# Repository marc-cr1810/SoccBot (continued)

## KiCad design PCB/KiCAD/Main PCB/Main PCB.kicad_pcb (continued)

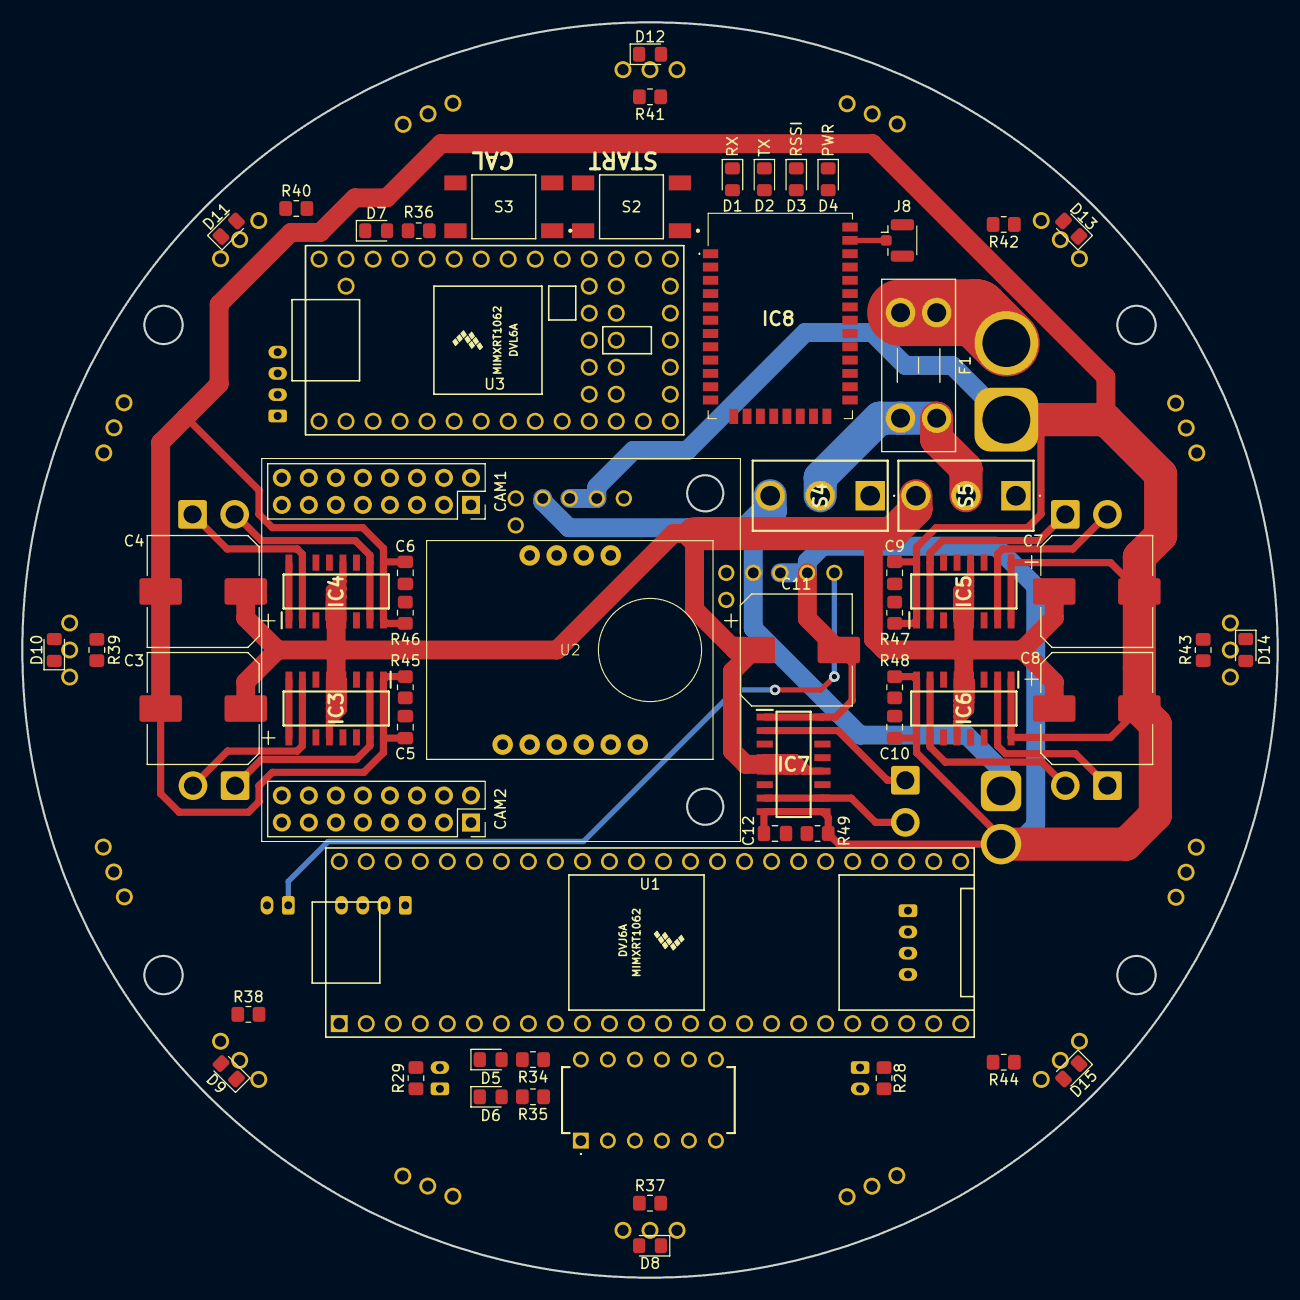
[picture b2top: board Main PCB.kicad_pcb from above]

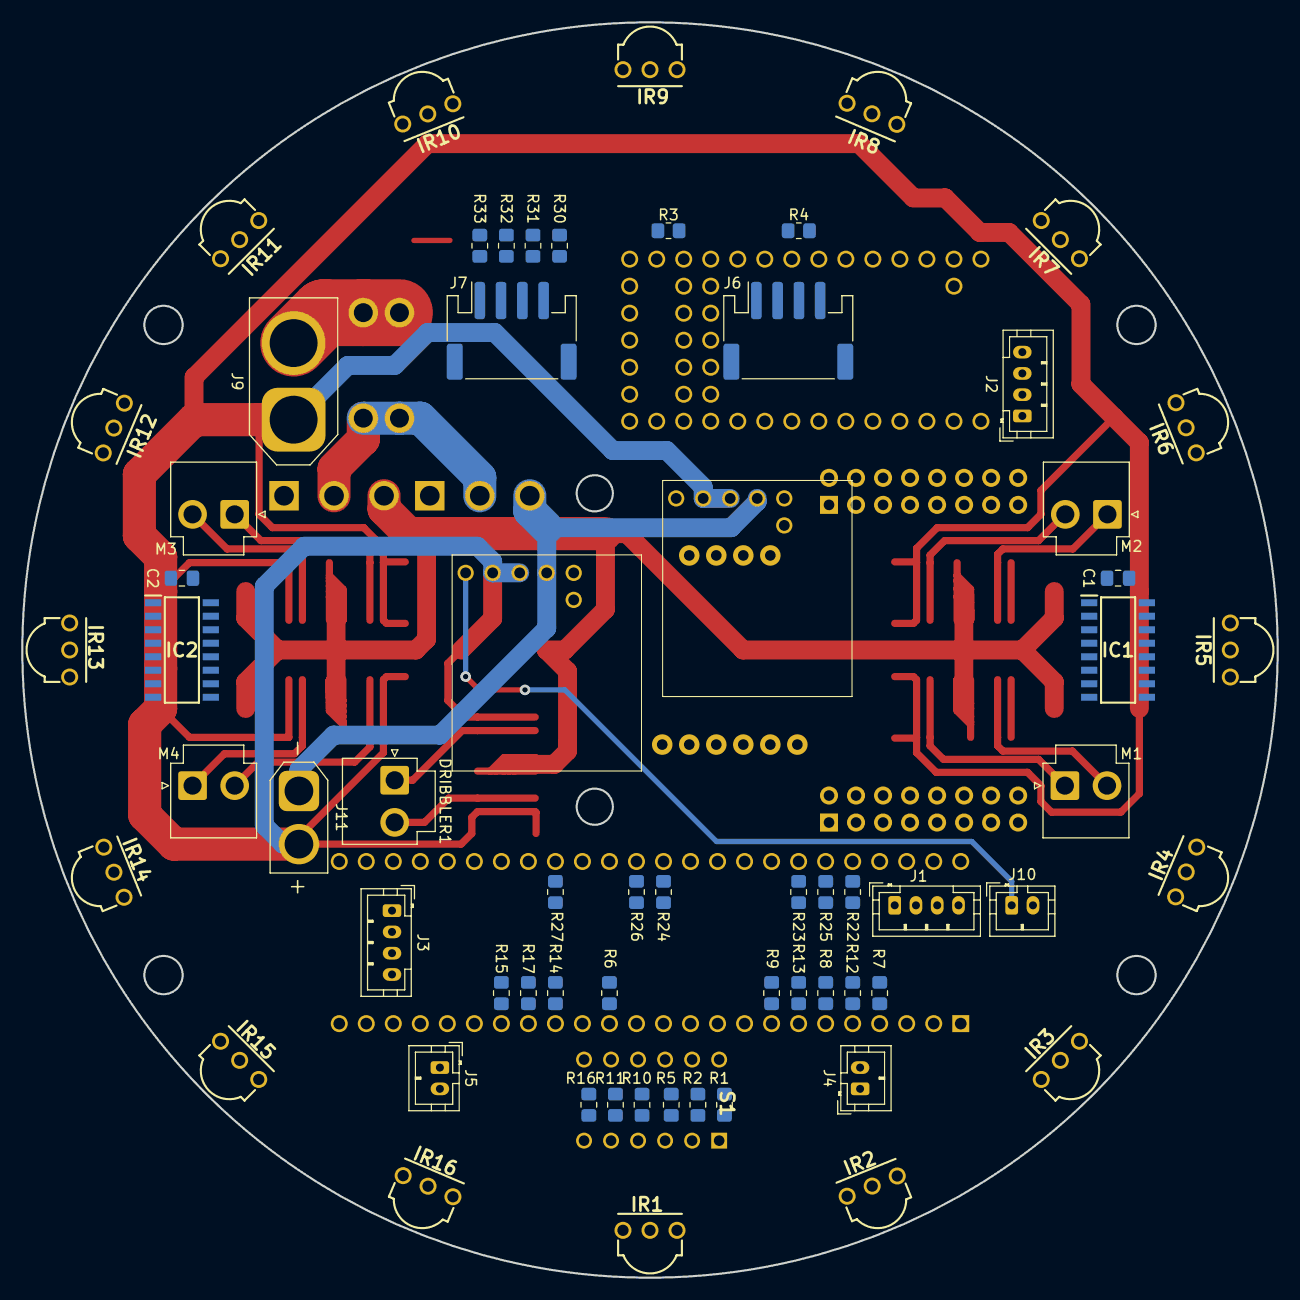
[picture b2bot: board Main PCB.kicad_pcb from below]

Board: 2 copper layers, 118.0 x 118.0 mm, 125 parts (64 on the bottom side), 138 nets.

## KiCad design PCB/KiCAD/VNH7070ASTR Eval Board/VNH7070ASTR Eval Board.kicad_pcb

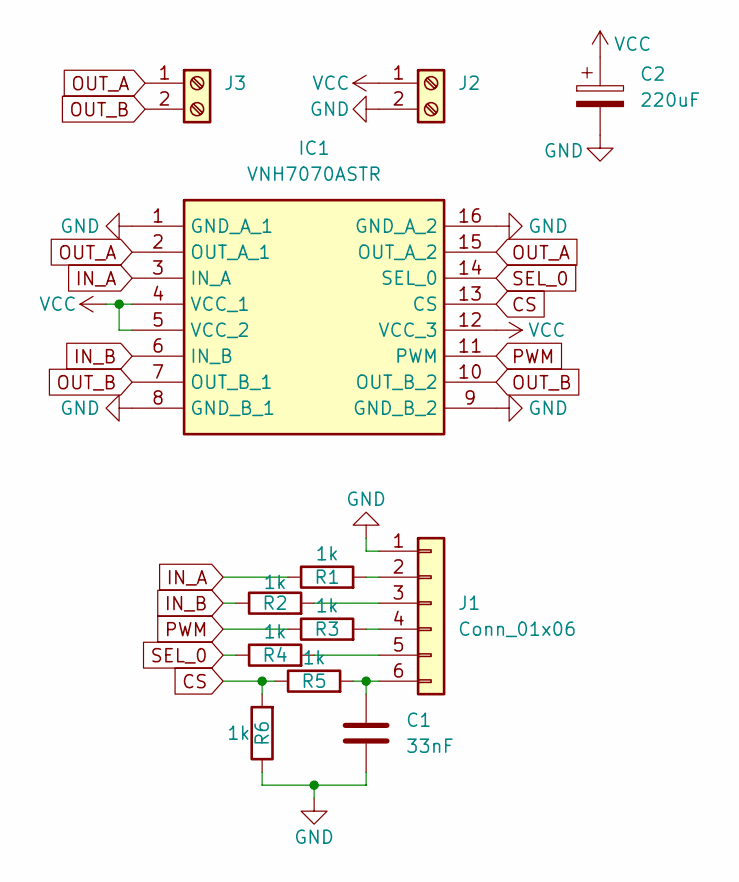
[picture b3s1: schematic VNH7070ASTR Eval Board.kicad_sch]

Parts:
C1: 33nF; C_0805_2012Metric_Pad1.18x1.45mm_HandSolder
C2: 220uF; CP_Elec_10x10
IC1: VNH7070ASTR; SOIC127P600X175-16N; Mouser Part Number 511-VNH7070ASTR
J1: Conn_01x06; PinHeader_1x06_P2.54mm_Vertical
J2, J3: Screw_Terminal_01x02; TerminalBlock_MaiXu_MX126-5.0-02P_1x02_P5.00mm
R1, R2, R3, R4, R5, R6: 1k; R_0805_2012Metric_Pad1.20x1.40mm_HandSolder

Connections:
CS: IC1.13 (CS), R5.1, R6.2
GND: C1.2, C2.2, IC1.1 (GND_A_1), IC1.8 (GND_B_1), IC1.9 (GND_B_2), IC1.16 (GND_A_2), J1.1, J2.2, R6.1
IN_A: IC1.3 (IN_A), R1.1
IN_B: IC1.6 (IN_B), R2.1
unnamed: J1.2, R1.2
unnamed: J1.3, R2.2
unnamed: J1.4, R3.2
unnamed: J1.5, R4.2
unnamed: C1.1, J1.6, R5.2
OUT_A: IC1.2 (OUT_A_1), IC1.15 (OUT_A_2), J3.1
OUT_B: IC1.7 (OUT_B_1), IC1.10 (OUT_B_2), J3.2
PWM: IC1.11 (PWM), R3.1
SEL_0: IC1.14 (SEL_0), R4.1
VCC: C2.1, IC1.4 (VCC_1), IC1.5 (VCC_2), IC1.12 (VCC_3), J2.1

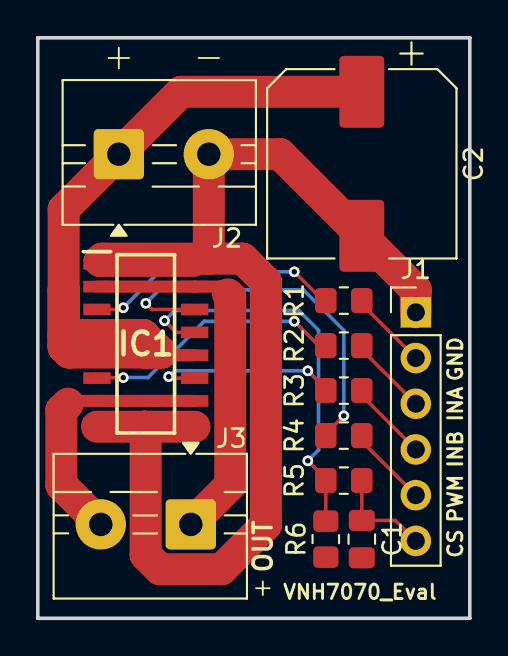
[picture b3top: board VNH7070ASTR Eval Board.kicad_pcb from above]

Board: 2 copper layers, 24.0 x 32.2 mm, 12 parts (0 on the bottom side), 14 nets.

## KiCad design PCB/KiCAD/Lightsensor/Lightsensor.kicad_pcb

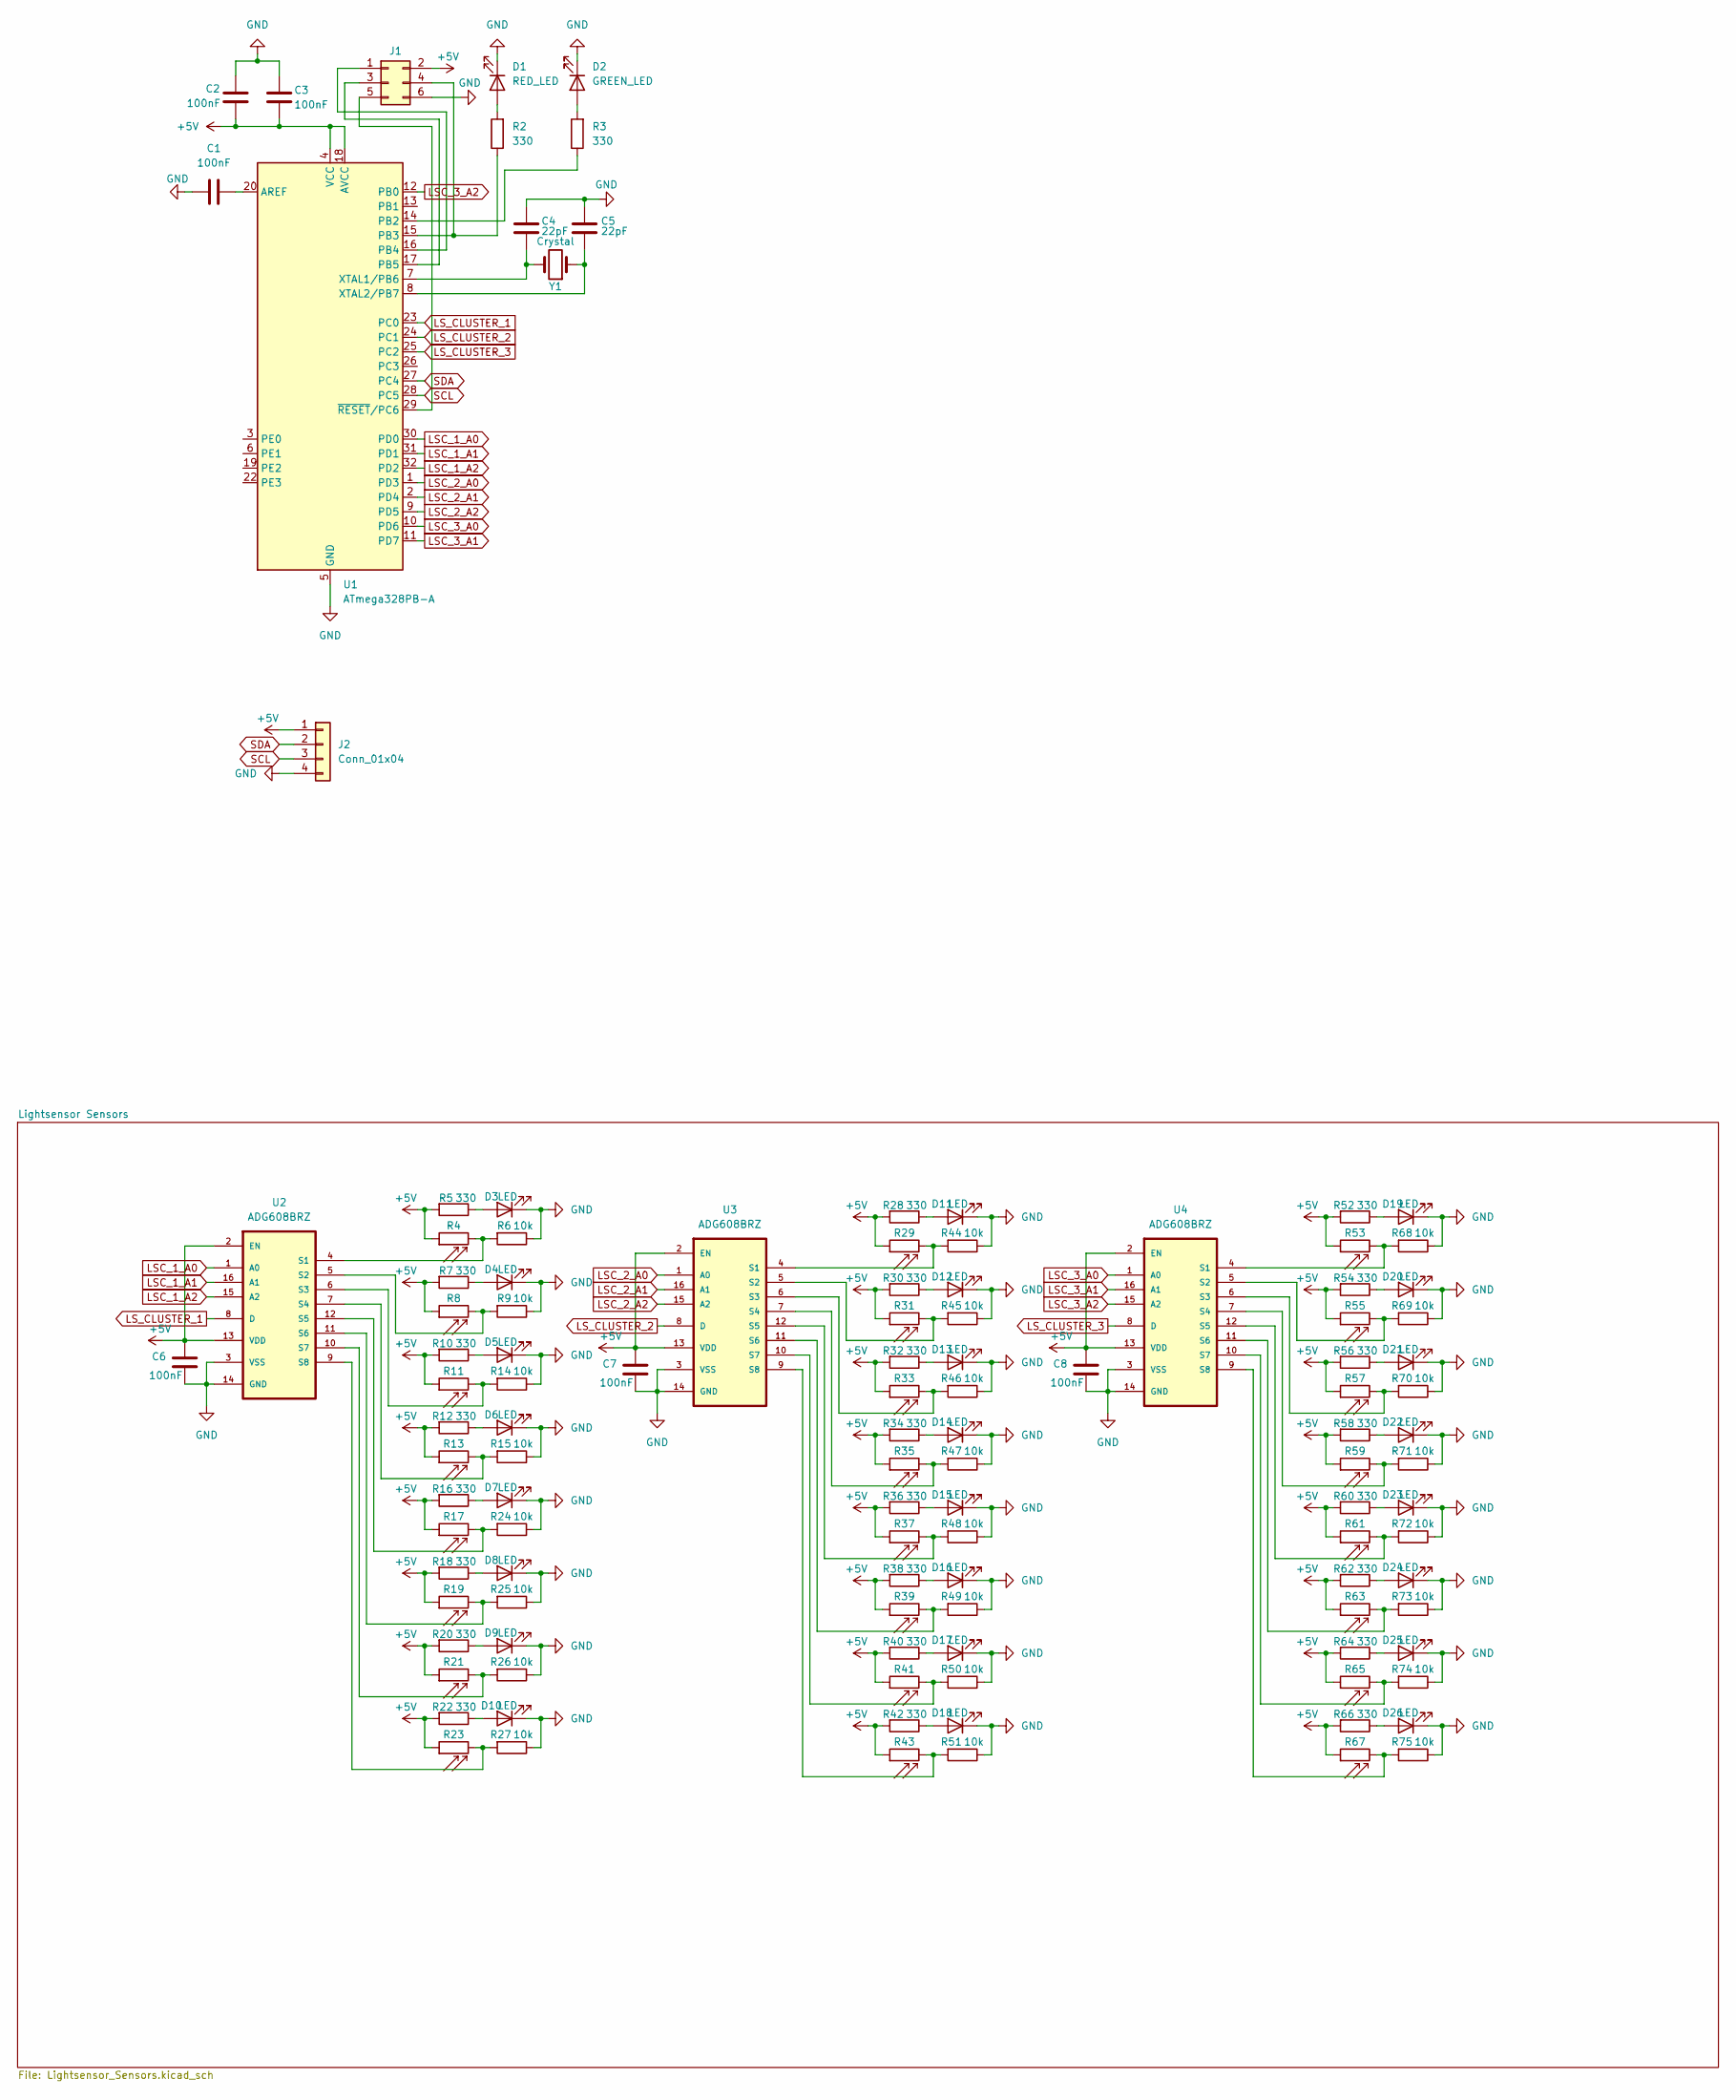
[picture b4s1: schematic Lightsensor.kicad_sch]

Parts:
C1, C2, C3, C6, C7, C8: 100nF; C_0805_2012Metric_Pad1.18x1.45mm_HandSolder
C4, C5: 22pF; C_0805_2012Metric_Pad1.18x1.45mm_HandSolder
D1: RED_LED; LED_0805_2012Metric_Pad1.15x1.40mm_HandSolder
D2: GREEN_LED; LED_0805_2012Metric_Pad1.15x1.40mm_HandSolder
D3, D4, D5, D6, D7, D8, D9, D10, D11, D12, D13, D14, D15, D16, D17, D18, D19, D20, D21, D22, D23, D24, D25, D26: LED; LED_SMD_3mm
J1: Conn_02x03_Odd_Even; IDC-Header_2x03_P2.54mm_Vertical_SMD
J2: Conn_01x04; JST_PH_B4B-PH-SM4-TB_1x04-1MP_P2.00mm_Vertical
R2, R3, R5, R7, R10, R12, R16, R18, R20, R22, R28, R30, R32, R34, R36, R38, R40, R42, R52, R54, R56, R58, R60, R62, R64, R66: 330; R_0805_2012Metric_Pad1.20x1.40mm_HandSolder
R4, R8, R11, R13, R17, R19, R21, R23, R29, R31, R33, R35, R37, R39, R41, R43, R53, R55, R57, R59, R61, R63, R65, R67: R_Photo; Photoresistor_SMD_5mm
R6, R9, R14, R15, R24, R25, R26, R27, R44, R45, R46, R47, R48, R49, R50, R51, R68, R69, R70, R71, R72, R73, R74, R75: 10k; R_0805_2012Metric_Pad1.20x1.40mm_HandSolder
U1: ATmega328PB-A; TQFP-32_7x7mm_P0.8mm
U2, U3, U4: ADG608BRZ; MPN ADG608BRUZ
Y1: Crystal; Crystal_SMD_HC49-SD

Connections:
+5V: C2.2, C3.2, C6.1, C7.1, C8.1, J1.2, J2.1, R4.1, R5.2, R7.2, R8.1, R10.2, R11.1, R12.2, R13.1, R16.2, R17.1, R18.2, R19.1, R20.2, R21.1, R22.2, R23.1, R28.2, R29.1, R30.2, R31.1, R32.2, R33.1, R34.2, R35.1, R36.2, R37.1, R38.2, R39.1, R40.2, R41.1, R42.2, R43.1, R52.2, R53.1, R54.2, R55.1, R56.2, R57.1, R58.2, R59.1, R60.2, R61.1, R62.2, R63.1, R64.2, R65.1, R66.2, R67.1, U1.4 (VCC), U1.18 (AVCC), U2.2 (EN), U2.13 (VDD), U3.2 (EN), U3.13 (VDD), U4.2 (EN), U4.13 (VDD)
GND: C1.2, C2.1, C3.1, C4.1, C5.1, C6.2, C7.2, C8.2, D1.1 (K), D2.1 (K), D3.1 (K), D4.1 (K), D5.1 (K), D6.1 (K), D7.1 (K), D8.1 (K), D9.1 (K), D10.1 (K), D11.1 (K), D12.1 (K), D13.1 (K), D14.1 (K), D15.1 (K), D16.1 (K), D17.1 (K), D18.1 (K), D19.1 (K), D20.1 (K), D21.1 (K), D22.1 (K), D23.1 (K), D24.1 (K), D25.1 (K), D26.1 (K), J1.6, J2.4, R6.1, R9.1, R14.1, R15.1, R24.1, R25.1, R26.1, R27.1, R44.1, R45.1, R46.1, R47.1, R48.1, R49.1, R50.1, R51.1, R68.1, R69.1, R70.1, R71.1, R72.1, R73.1, R74.1, R75.1, U1.5 (GND), U1.21 (GND), U2.3 (VSS), U2.14 (GND), U3.3 (VSS), U3.14 (GND), U4.3 (VSS), U4.14 (GND)
LSC_1_A0: U1.30 (PD0), U2.1 (A0)
LSC_1_A1: U1.31 (PD1), U2.16 (A1)
LSC_1_A2: U1.32 (PD2), U2.15 (A2)
LSC_2_A0: U1.1 (PD3), U3.1 (A0)
LSC_2_A1: U1.2 (PD4), U3.16 (A1)
LSC_2_A2: U1.9 (PD5), U3.15 (A2)
LSC_3_A0: U1.10 (PD6), U4.1 (A0)
LSC_3_A1: U1.11 (PD7), U4.16 (A1)
LSC_3_A2: U1.12 (PB0), U4.15 (A2)
LS_CLUSTER_1: U1.23 (PC0), U2.8 (D)
LS_CLUSTER_2: U1.24 (PC1), U3.8 (D)
LS_CLUSTER_3: U1.25 (PC2), U4.8 (D)
unnamed: D1.2 (A), R2.2
unnamed: D2.2 (A), R3.2
unnamed: D3.2 (A), R5.1
unnamed: D4.2 (A), R7.1
unnamed: D5.2 (A), R10.1
unnamed: D6.2 (A), R12.1
unnamed: D7.2 (A), R16.1
unnamed: D8.2 (A), R18.1
unnamed: D9.2 (A), R20.1
unnamed: D10.2 (A), R22.1
unnamed: D11.2 (A), R28.1
unnamed: D12.2 (A), R30.1
unnamed: D13.2 (A), R32.1
unnamed: D14.2 (A), R34.1
unnamed: D15.2 (A), R36.1
unnamed: D16.2 (A), R38.1
unnamed: D17.2 (A), R40.1
unnamed: D18.2 (A), R42.1
unnamed: D19.2 (A), R52.1
unnamed: D20.2 (A), R54.1
unnamed: D21.2 (A), R56.1
unnamed: D22.2 (A), R58.1
unnamed: D23.2 (A), R60.1
unnamed: D24.2 (A), R62.1
unnamed: D25.2 (A), R64.1
unnamed: D26.2 (A), R66.1
unnamed: J1.1, U1.16 (PB4)
unnamed: J1.3, U1.17 (PB5)
unnamed: J1.4, R2.1, U1.15 (PB3)
unnamed: J1.5, U1.29 (~RESET/PC6)
unnamed: C1.1, U1.20 (AREF)
unnamed: R3.1, U1.14 (PB2)
unnamed: C4.2, U1.7 (XTAL1/PB6), Y1.2
unnamed: C5.2, U1.8 (XTAL2/PB7), Y1.1
unnamed: R4.2, R6.2, U2.4 (S1)
unnamed: R8.2, R9.2, U2.5 (S2)
unnamed: R11.2, R14.2, U2.6 (S3)
unnamed: R13.2, R15.2, U2.7 (S4)
unnamed: R17.2, R24.2, U2.12 (S5)
unnamed: R19.2, R25.2, U2.11 (S6)
unnamed: R21.2, R26.2, U2.10 (S7)
unnamed: R23.2, R27.2, U2.9 (S8)
unnamed: R29.2, R44.2, U3.4 (S1)
unnamed: R31.2, R45.2, U3.5 (S2)
unnamed: R33.2, R46.2, U3.6 (S3)
unnamed: R35.2, R47.2, U3.7 (S4)
unnamed: R37.2, R48.2, U3.12 (S5)
unnamed: R39.2, R49.2, U3.11 (S6)
unnamed: R41.2, R50.2, U3.10 (S7)
unnamed: R43.2, R51.2, U3.9 (S8)
unnamed: R53.2, R68.2, U4.4 (S1)
unnamed: R55.2, R69.2, U4.5 (S2)
unnamed: R57.2, R70.2, U4.6 (S3)
unnamed: R59.2, R71.2, U4.7 (S4)
unnamed: R61.2, R72.2, U4.12 (S5)
unnamed: R63.2, R73.2, U4.11 (S6)
unnamed: R65.2, R74.2, U4.10 (S7)
unnamed: R67.2, R75.2, U4.9 (S8)
SCL: J2.3, U1.28 (PC5)
SDA: J2.2, U1.27 (PC4)

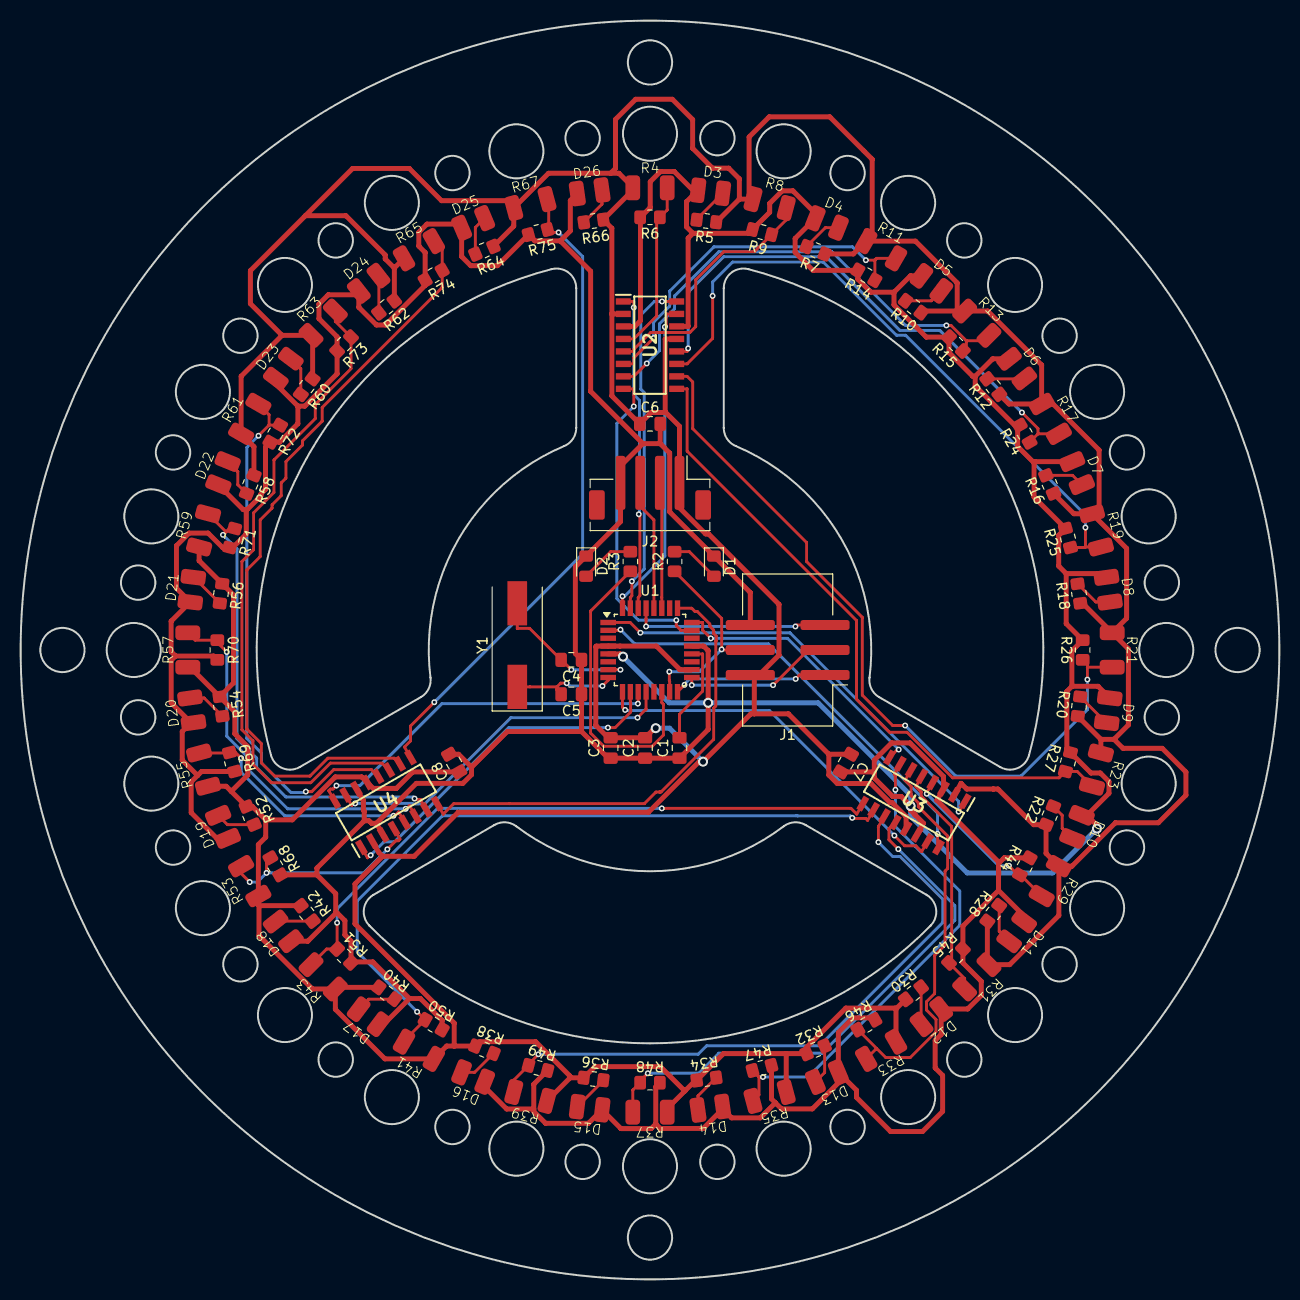
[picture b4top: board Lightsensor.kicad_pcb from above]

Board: 2 copper layers, 128.0 x 128.0 mm, 115 parts (0 on the bottom side), 74 nets.

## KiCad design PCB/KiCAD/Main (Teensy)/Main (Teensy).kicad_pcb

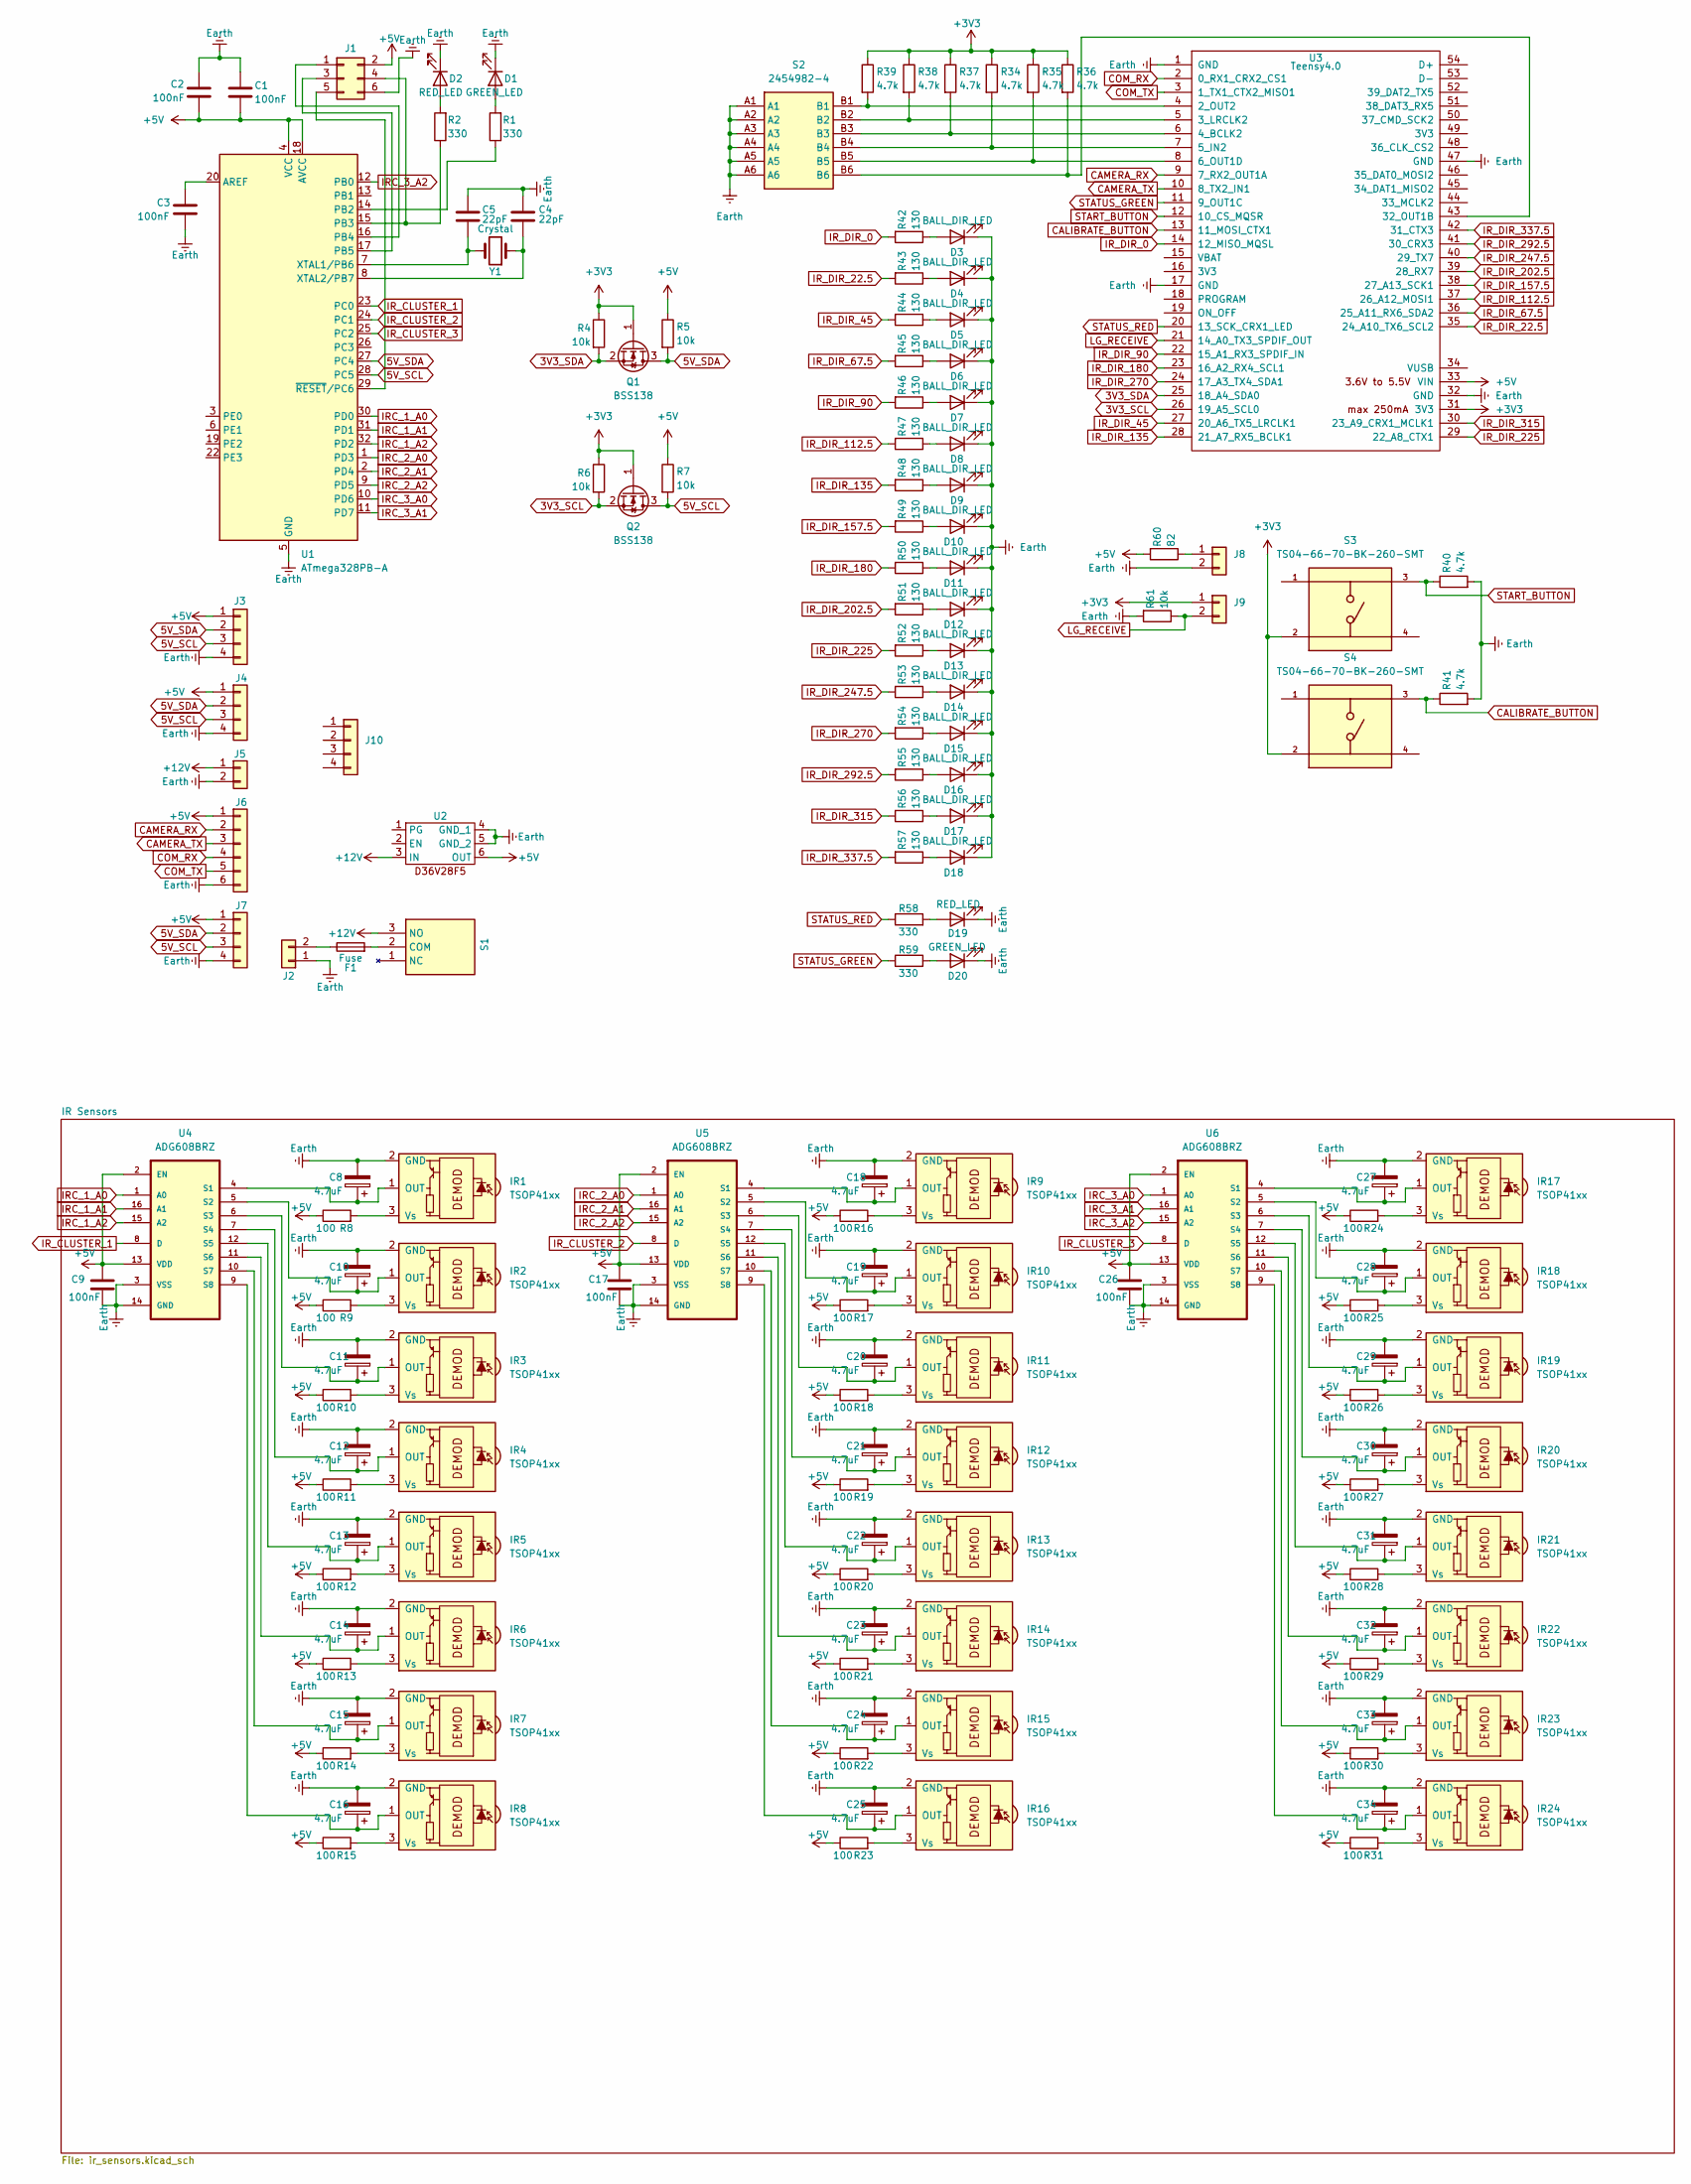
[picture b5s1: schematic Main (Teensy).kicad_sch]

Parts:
C1, C2, C3, C9, C17, C26: 100nF; C_0805_2012Metric_Pad1.18x1.45mm_HandSolder
C4, C5: 22pF; C_0805_2012Metric_Pad1.18x1.45mm_HandSolder
C8, C10, C11, C12, C13, C14, C15, C16, C18, C19, C20, C21, C22, C23, C24, C25, C27, C28, C29, C30, C31, C32, C33, C34: 4.7uF; CP_Radial_D5.0mm_P2.00mm
D1, D20: GREEN_LED; LED_0805_2012Metric_Pad1.15x1.40mm_HandSolder
D2, D19: RED_LED; LED_0805_2012Metric_Pad1.15x1.40mm_HandSolder
D3, D4, D5, D6, D7, D8, D9, D10, D11, D12, D13, D14, D15, D16, D17, D18: BALL_DIR_LED; LED_0805_2012Metric_Pad1.15x1.40mm_HandSolder
F1: Fuse; Fuseholder_Blade_Mini_Keystone_3568
IR1, IR2, IR3, IR4, IR5, IR6, IR7, IR8, IR9, IR10, IR11, IR12, IR13, IR14, IR15, IR16, IR17, IR18, IR19, IR20, IR21, IR22, IR23, IR24: TSOP41xx; Vishay_CUSTOM-3Pin
J1: Conn_02x03_Odd_Even; IDC-Header_2x03_P2.54mm_Vertical_SMD
J2: Conn_01x02; AMASS_XT60-M_1x02_P7.20mm_Vertical
J3, J4, J7: Conn_01x04; JST_PH_B4B-PH-K_1x04_P2.00mm_Vertical
J5: Conn_01x02; Molex_KK-254_AE-6410-02A_1x02_P2.54mm_Vertical
J6: Conn_01x06; JST_PH_B6B-PH-K_1x06_P2.00mm_Vertical
J8, J9: Conn_01x02; JST_PH_B2B-PH-K_1x02_P2.00mm_Vertical
J10: Conn_01x04; JST_XH_B4B-XH-A_1x04_P2.50mm_Vertical
Q1, Q2: BSS138; SOT-23
R1, R2, R58, R59: 330; R_0805_2012Metric_Pad1.20x1.40mm_HandSolder
R4, R5, R6, R7, R61: 10k; R_0805_2012Metric_Pad1.20x1.40mm_HandSolder
R8, R9, R10, R11, R12, R13, R14, R15, R16, R17, R18, R19, R20, R21, R22, R23, R24, R25, R26, R27, R28, R29, R30, R31: 100; R_0805_2012Metric_Pad1.20x1.40mm_HandSolder
R34, R35, R36, R37, R38, R39, R40, R41: 4.7k; R_0805_2012Metric_Pad1.20x1.40mm_HandSolder
R42, R43, R44, R45, R46, R47, R48, R49, R50, R51, R52, R53, R54, R55, R56, R57: 130; R_0805_2012Metric_Pad1.20x1.40mm_HandSolder
R60: 82; R_0805_2012Metric_Pad1.20x1.40mm_HandSolder
S1: 1101M2S3CGE2; Mouser Part Number 611-1101M2S3CGE2
S2: 2454982-4; DIP_6_SWITCH_THT; Mouser Part Number 655-2454982-4
S3, S4: TS04-66-70-BK-260-SMT; SW_TS04-66-70-BK-260-SMT; PARTREV 1.0
U1: ATmega328PB-A; TQFP-32_7x7mm_P0.8mm
U2: D36V28F5
U3: Teensy4.0; Teensy40
U4, U5, U6: ADG608BRZ; MPN ADG608BRUZ
Y1: Crystal; Crystal_SMD_HC49-SD

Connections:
3V3_SCL: Q2.2 (S), R6.2, U3.26 (19_A5_SCL0)
3V3_SDA: Q1.2 (S), R4.2, U3.25 (18_A4_SDA0)
5V_SCL: J3.3, J4.3, J7.3, Q2.3 (D), R7.2, U1.28 (PC5)
5V_SDA: J3.2, J4.2, J7.2, Q1.3 (D), R5.2, U1.27 (PC4)
+3V3: J9.1, Q1.1 (G), Q2.1 (G), R4.1, R6.1, R34.1, R35.1, R36.1, R37.1, R38.1, R39.1, S3.2, S4.2, U3.31 (3V3)
+5V: C1.2, C2.2, C9.1, C17.1, C26.1, J1.2, J3.1, J4.1, J6.1, J7.1, R5.1, R7.1, R8.1, R9.1, R10.1, R11.1, R12.1, R13.1, R14.1, R15.1, R16.1, R17.1, R18.1, R19.1, R20.1, R21.1, R22.1, R23.1, R24.1, R25.1, R26.1, R27.1, R28.1, R29.1, R30.1, R31.1, R60.2, U1.4 (VCC), U1.18 (AVCC), U2.6 (OUT), U3.33 (VIN), U4.2 (EN), U4.13 (VDD), U5.2 (EN), U5.13 (VDD), U6.2 (EN), U6.13 (VDD)
+12V: J5.1, S1.3 (NO), U2.3 (IN)
CALIBRATE_BUTTON: R41.1, S4.3, U3.13 (11_MOSI_CTX1)
CAMERA_RX: J6.2, U3.9 (7_RX2_OUT1A)
CAMERA_TX: J6.3, U3.10 (8_TX2_IN1)
COM_RX: J6.4, U3.2 (0_RX1_CRX2_CS1)
COM_TX: J6.5, U3.3 (1_TX1_CTX2_MISO1)
Earth: C1.1, C2.1, C3.2, C4.1, C5.1, C8.2, C9.2, C10.2, C11.2, C12.2, C13.2, C14.2, C15.2, C16.2, C17.2, C18.2, C19.2, C20.2, C21.2, C22.2, C23.2, C24.2, C25.2, C26.2, C27.2, C28.2, C29.2, C30.2, C31.2, C32.2, C33.2, C34.2, D1.1 (K), D2.1 (K), D3.1 (K), D4.1 (K), D5.1 (K), D6.1 (K), D7.1 (K), D8.1 (K), D9.1 (K), D10.1 (K), D11.1 (K), D12.1 (K), D13.1 (K), D14.1 (K), D15.1 (K), D16.1 (K), D17.1 (K), D18.1 (K), D19.1 (K), D20.1 (K), IR1.2 (GND), IR2.2 (GND), IR3.2 (GND), IR4.2 (GND), IR5.2 (GND), IR6.2 (GND), IR7.2 (GND), IR8.2 (GND), IR9.2 (GND), IR10.2 (GND), IR11.2 (GND), IR12.2 (GND), IR13.2 (GND), IR14.2 (GND), IR15.2 (GND), IR16.2 (GND), IR17.2 (GND), IR18.2 (GND), IR19.2 (GND), IR20.2 (GND), IR21.2 (GND), IR22.2 (GND), IR23.2 (GND), IR24.2 (GND), J1.6, J2.1, J3.4, J4.4, J5.2, J6.6, J7.4, J8.2, R40.2, R41.2, R61.2, S2.A1, S2.A2, S2.A3, S2.A4, S2.A5, S2.A6, U1.5 (GND), U1.21 (GND), U2.4 (GND_1), U2.5 (GND_2), U3.1 (GND), U3.17 (GND), U3.32 (GND), U3.47 (GND), U4.3 (VSS), U4.14 (GND), U5.3 (VSS), U5.14 (GND), U6.3 (VSS), U6.14 (GND)
IRC_1_A0: U1.30 (PD0), U4.1 (A0)
IRC_1_A1: U1.31 (PD1), U4.16 (A1)
IRC_1_A2: U1.32 (PD2), U4.15 (A2)
IRC_2_A0: U1.1 (PD3), U5.1 (A0)
IRC_2_A1: U1.2 (PD4), U5.16 (A1)
IRC_2_A2: U1.9 (PD5), U5.15 (A2)
IRC_3_A0: U1.10 (PD6), U6.1 (A0)
IRC_3_A1: U1.11 (PD7), U6.16 (A1)
IRC_3_A2: U1.12 (PB0), U6.15 (A2)
IR_CLUSTER_1: U1.23 (PC0), U4.8 (D)
IR_CLUSTER_2: U1.24 (PC1), U5.8 (D)
IR_CLUSTER_3: U1.25 (PC2), U6.8 (D)
IR_DIR_0: R42.2, U3.14 (12_MISO_MQSL)
IR_DIR_22.5: R43.2, U3.35 (24_A10_TX6_SCL2)
IR_DIR_45: R44.2, U3.27 (20_A6_TX5_LRCLK1)
IR_DIR_67.5: R45.2, U3.36 (25_A11_RX6_SDA2)
IR_DIR_90: R46.2, U3.22 (15_A1_RX3_SPDIF_IN)
IR_DIR_112.5: R47.2, U3.37 (26_A12_MOSI1)
IR_DIR_135: R48.2, U3.28 (21_A7_RX5_BCLK1)
IR_DIR_157.5: R49.2, U3.38 (27_A13_SCK1)
IR_DIR_180: R50.2, U3.23 (16_A2_RX4_SCL1)
IR_DIR_202.5: R51.2, U3.39 (28_RX7)
IR_DIR_225: R52.2, U3.29 (22_A8_CTX1)
IR_DIR_247.5: R53.2, U3.40 (29_TX7)
IR_DIR_270: R54.2, U3.24 (17_A3_TX4_SDA1)
IR_DIR_292.5: R55.2, U3.41 (30_CRX3)
IR_DIR_315: R56.2, U3.30 (23_A9_CRX1_MCLK1)
IR_DIR_337.5: R57.2, U3.42 (31_CTX3)
LG_RECEIVE: J9.2, R61.1, U3.21 (14_A0_TX3_SPDIF_OUT)
unnamed: D1.2 (A), R1.2
unnamed: D2.2 (A), R2.2
unnamed: D3.2 (A), R42.1
unnamed: D4.2 (A), R43.1
unnamed: D5.2 (A), R44.1
unnamed: D6.2 (A), R45.1
unnamed: D7.2 (A), R46.1
unnamed: D8.2 (A), R47.1
unnamed: D9.2 (A), R48.1
unnamed: D10.2 (A), R49.1
unnamed: D11.2 (A), R50.1
unnamed: D12.2 (A), R51.1
unnamed: D13.2 (A), R52.1
unnamed: D14.2 (A), R53.1
unnamed: D15.2 (A), R54.1
unnamed: D16.2 (A), R55.1
unnamed: D17.2 (A), R56.1
unnamed: D18.2 (A), R57.1
unnamed: D19.2 (A), R58.2
unnamed: D20.2 (A), R59.2
unnamed: C8.1, IR1.1 (OUT), U4.4 (S1)
unnamed: IR1.3 (Vs), R8.2
unnamed: C10.1, IR2.1 (OUT), U4.5 (S2)
unnamed: IR2.3 (Vs), R9.2
unnamed: C11.1, IR3.1 (OUT), U4.6 (S3)
unnamed: IR3.3 (Vs), R10.2
unnamed: C12.1, IR4.1 (OUT), U4.7 (S4)
unnamed: IR4.3 (Vs), R11.2
unnamed: C13.1, IR5.1 (OUT), U4.12 (S5)
unnamed: IR5.3 (Vs), R12.2
unnamed: C14.1, IR6.1 (OUT), U4.11 (S6)
unnamed: IR6.3 (Vs), R13.2
unnamed: C15.1, IR7.1 (OUT), U4.10 (S7)
unnamed: IR7.3 (Vs), R14.2
unnamed: C16.1, IR8.1 (OUT), U4.9 (S8)
unnamed: IR8.3 (Vs), R15.2
unnamed: C18.1, IR9.1 (OUT), U5.4 (S1)
unnamed: IR9.3 (Vs), R16.2
unnamed: C19.1, IR10.1 (OUT), U5.5 (S2)
unnamed: IR10.3 (Vs), R17.2
unnamed: C20.1, IR11.1 (OUT), U5.6 (S3)
unnamed: IR11.3 (Vs), R18.2
unnamed: C21.1, IR12.1 (OUT), U5.7 (S4)
unnamed: IR12.3 (Vs), R19.2
unnamed: C22.1, IR13.1 (OUT), U5.12 (S5)
unnamed: IR13.3 (Vs), R20.2
unnamed: C23.1, IR14.1 (OUT), U5.11 (S6)
unnamed: IR14.3 (Vs), R21.2
unnamed: C24.1, IR15.1 (OUT), U5.10 (S7)
unnamed: IR15.3 (Vs), R22.2
unnamed: C25.1, IR16.1 (OUT), U5.9 (S8)
unnamed: IR16.3 (Vs), R23.2
unnamed: C27.1, IR17.1 (OUT), U6.4 (S1)
unnamed: IR17.3 (Vs), R24.2
unnamed: C28.1, IR18.1 (OUT), U6.5 (S2)
unnamed: IR18.3 (Vs), R25.2
unnamed: C29.1, IR19.1 (OUT), U6.6 (S3)
unnamed: IR19.3 (Vs), R26.2
unnamed: C30.1, IR20.1 (OUT), U6.7 (S4)
unnamed: IR20.3 (Vs), R27.2
unnamed: C31.1, IR21.1 (OUT), U6.12 (S5)
unnamed: IR21.3 (Vs), R28.2
unnamed: C32.1, IR22.1 (OUT), U6.11 (S6)
unnamed: IR22.3 (Vs), R29.2
unnamed: C33.1, IR23.1 (OUT), U6.10 (S7)
unnamed: IR23.3 (Vs), R30.2
unnamed: C34.1, IR24.1 (OUT), U6.9 (S8)
unnamed: IR24.3 (Vs), R31.2
unnamed: J1.1, U1.16 (PB4)
unnamed: J1.3, U1.17 (PB5)
unnamed: J1.4, R2.1, U1.15 (PB3)
unnamed: J1.5, U1.29 (~RESET/PC6)
unnamed: F1.1, J2.2
unnamed: J8.1, R60.1
unnamed: F1.2, S1.2 (COM)
unnamed: C3.1, U1.20 (AREF)
unnamed: R1.1, U1.14 (PB2)
unnamed: C5.2, U1.7 (XTAL1/PB6), Y1.2
unnamed: C4.2, U1.8 (XTAL2/PB7), Y1.1
unnamed: R39.2, S2.B1, U3.4 (2_OUT2)
unnamed: R38.2, S2.B2, U3.5 (3_LRCLK2)
unnamed: R37.2, S2.B3, U3.6 (4_BCLK2)
unnamed: R34.2, S2.B4, U3.7 (5_IN2)
unnamed: R35.2, S2.B5, U3.8 (6_OUT1D)
unnamed: R36.2, S2.B6, U3.43 (32_OUT1B)
START_BUTTON: R40.1, S3.3, U3.12 (10_CS_MQSR)
STATUS_GREEN: R59.1, U3.11 (9_OUT1C)
STATUS_RED: R58.1, U3.20 (13_SCK_CRX1_LED)
